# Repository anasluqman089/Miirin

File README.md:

# Miirin

Miirin is a compact MP3 player built around a Seeed XIAO ESP32-S3 and a
DFPlayer Pro. It has an OLED display, five buttons, a rotary encoder, and an
RGB status LED. The `CAD`, `PCB`, and `Production` folders contain the
enclosure, board, and manufacturing files.

## Bill of materials

| Quantity | Reference | Part | Prices ($) | Buy Links |
| :---: | :---: | :--- | :---: | :--- |
| 1 | U1 | Seeed XIAO ESP32-S3 module | 7.50 | [AliExpress](https://www.aliexpress.com/w/wholesale-Seeed-XIAO-ESP32-S3-module.html) |
| 1 | U2 | DFRobot DFPlayer Pro (DFR0768) | 8.50 | [AliExpress](https://www.aliexpress.com/w/wholesale-DFRobot-DFPlayer-Pro-DFR0768.html) |
| 1 | - | 1.3 Inch OLED screen | 3.50 | [AliExpress](https://www.aliexpress.com/w/wholesale-1.3-Inch-OLED-screen.html) |
| 1 | U3 | PCF8574P I2C I/O expander | 1.20 | [AliExpress](https://www.aliexpress.com/w/wholesale-PCF8574P-I2C-IO-expander.html) |
| 1 | D1 | Common-anode RGB LED | 0.35 | [AliExpress](https://www.aliexpress.com/w/wholesale-Common-anode-RGB-LED.html) |
| 1 | Q1 | P-channel MOSFET | 0.80 | [AliExpress](https://www.aliexpress.com/w/wholesale-P-channel-MOSFET.html) |
| 1 | SW6 | Rotary encoder | 0.60 | [AliExpress](https://www.aliexpress.com/w/wholesale-Rotary-encoder.html) |
| 1 | SW5 | Momentary push buttons | 0.15 | [AliExpress](https://www.aliexpress.com/w/wholesale-Momentary-push-buttons.html) |
| 4 | SW1-SW4 | Cherry MX Keyboard Switches | 2.00 | [AliExpress](https://www.aliexpress.com/w/wholesale-Cherry-MX-switch.html) |
| 1 | J1 | 4-pin socket/header for the OLED | 0.10 | [AliExpress](https://www.aliexpress.com/w/wholesale-4-pin-socket-header-for-the-OLED.html) |
| 1 | J2 | Switched 3.5 mm audio jack | 0.50 | [AliExpress](https://www.aliexpress.com/w/wholesale-Switched-3.5-mm-audio-jack.html) |
| 3 | R4-R6 | 220 Ohm resistors | 0.15 | [AliExpress](https://www.aliexpress.com/w/wholesale-220-Ohm-resistors.html) |
| 2 | R2-R3 | 4.7 kOhm resistors | 0.10 | [AliExpress](https://www.aliexpress.com/w/wholesale-4.7-kOhm-resistors.html) |
| 1 | R1 | 100 kOhm resistor | 0.05 | [AliExpress](https://www.aliexpress.com/w/wholesale-100-kOhm-resistor.html) |
| 2 | - | 100 kOhm resistors | 0.10 | [AliExpress](https://www.aliexpress.com/w/wholesale-100-kOhm-resistors.html) |
| 2 | C1-C2 | 10 uF ceramic capacitors | 0.30 | [AliExpress](https://www.aliexpress.com/w/wholesale-10-uF-ceramic-capacitors.html) |
| 1 | C4 | 0.1 uF ceramic capacitor | 0.10 | [AliExpress](https://www.aliexpress.com/w/wholesale-0.1-uF-ceramic-capacitor.html) |
| 1 | C5 | 470 uF polarized capacitor | 0.45 | [AliExpress](https://www.aliexpress.com/w/wholesale-470-uF-polarized-capacitor.html) |
| 3 | H1-H3 | M2 screw | 0.30 | [AliExpress](https://www.aliexpress.com/w/wholesale-M2-screw.html) |
| 5 | - | M2.5 screw | 0.50 | [AliExpress](https://www.aliexpress.com/w/wholesale-M2.5-screw.html) |
| 1 | - | PCB | 8.60 | - |
| 4 | - | 3D print | ~10.00 | - |
| **Total** | | | **$45.85** Not inluding shipping | |

## Controls and display

- **SW1:** Play or pause the current track.
- **SW2 / SW3:** Select the previous or next track. Selection wraps at either
  end of the list.
- **SW4:** Play the selected track.
- **Rotary encoder:** Adjust volume.
- **Hold SW5:** Pause playback and put the device into deep sleep. Press SW5 to
  wake it.

The OLED shows the current track, playback selection, volume, and battery
percentage. Battery percentage is an estimate based on cell voltage, not a
fuel-gauge measurement.

## Battery and RGB LED

Battery monitoring uses the divider wired to **D0**: battery positive goes through a 100 kΩ resistor to D0, then another 100 kΩ resistor connects D0 to battery negative (ground). The battery itself connects to the XIAO's battery pads.

The RGB LED is driven through the PCF8574 and indicates battery level:

- **Red:** Battery is at or below 20%
- **Green:** Battery is above 20%

Charging is not identified separately because the board has no charge-status
signal connected. The PCF8574 interrupt is connected to **D10**.

## Uploading code & audio files

Upload the code in firmware folder. Make sure to select the XIAO ESP32 S3 board.

Put your audio files on the DFPlayer Pro's storage. At startup, the player checks how many tracks are available and restores the last selected track and volume while the XIAO remains powered.

## CAD

Here is the link for the CAD
[Onshape](https://cad.onshape.com/documents/3d8e9b5928a29fef03f51911/w/7d3ee8411c85baeb3f6a489e/e/28521f022b7deb8d589466ae?renderMode=0&uiState=6ad3208a288b1a9cd259184f)

## Images

### Schematic

### PCB

### CAD

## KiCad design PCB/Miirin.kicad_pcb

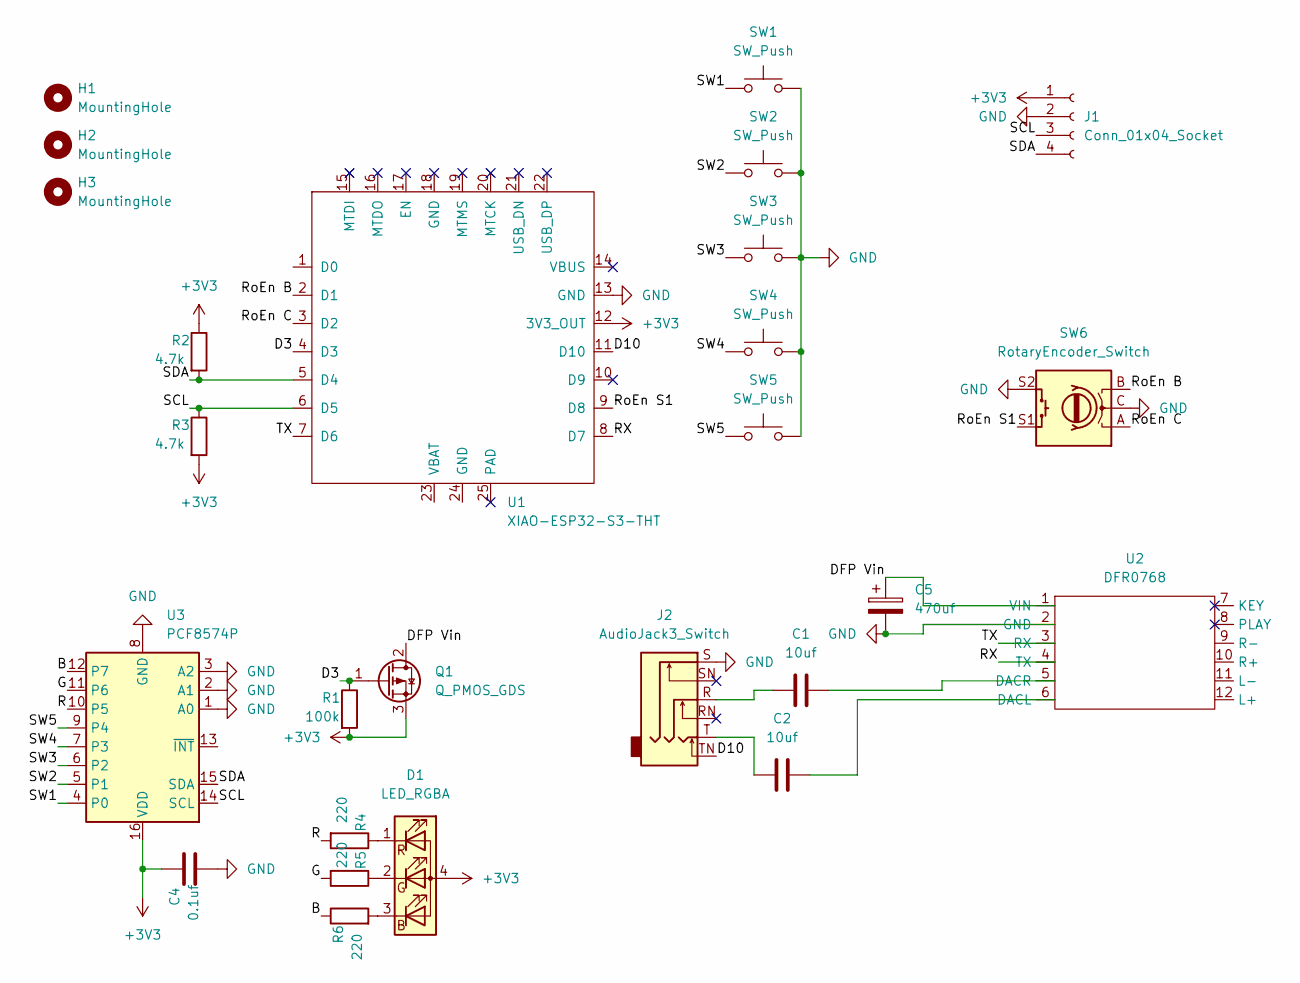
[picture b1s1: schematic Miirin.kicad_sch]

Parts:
C1, C2: 10uf; C_Disc_D4.3mm_W1.9mm_P5.00mm
C4: 0.1uf; C_Disc_D4.3mm_W1.9mm_P5.00mm
C5: 470uf; CP_Radial_D8.0mm_P3.50mm
D1: LED_RGBA; LED_D5.0mm-4_RGB
H1, H2, H3: MountingHole; MountingHole_2.2mm_M2
J1: Conn_01x04_Socket; PinHeader_1x04_P2.54mm_Horizontal
J2: AudioJack3_Switch; Jack_3.5mm_CUI_SJ1-3535NG_Horizontal
Q1: Q_PMOS_GDS; TO-92_Inline
R1: 100k; R_Axial_DIN0207_L6.3mm_D2.5mm_P10.16mm_Horizontal
R2, R3: 4.7k; R_Axial_DIN0207_L6.3mm_D2.5mm_P10.16mm_Horizontal
R4, R5, R6: 220; R_Axial_DIN0207_L6.3mm_D2.5mm_P10.16mm_Horizontal
SW1, SW2, SW3, SW4: SW_Push; SW_Cherry_MX_1.00u_PCB
SW5: SW_Push; SW_PUSH_6mm
SW6: RotaryEncoder_Switch; RotaryEncoder_Alps_EC11E-Switch_Vertical_H20mm
U1: XIAO-ESP32-S3-THT; XIAO-ESP32-S3-DIP
U2: DFR0768
U3: PCF8574P; DIP-16_W7.62mm

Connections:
+3V3: C4.2, D1.4 (A), J1.1, Q1.3 (S), R1.2, R2.1, R3.2, U1.12 (3V3_OUT), U3.16 (VDD)
/B: R6.1, U3.12 (P7)
/D3: Q1.1 (G), R1.1, U1.4 (D3)
/D10: J2.TN, U1.11 (D10)
/DFP Vin: C5.1, Q1.2 (D), U2.1 (VIN)
/G: R5.2, U3.11 (P6)
/R: R4.2, U3.10 (P5)
/RX: U1.8 (D7), U2.4 (TX)
/RoEn B: SW6.B, U1.2 (D1)
/RoEn C: SW6.A, U1.3 (D2)
/RoEn S1: SW6.S1, U1.9 (D8)
/SCL: J1.3, R3.1, U1.6 (D5), U3.14 (SCL)
/SDA: J1.4, R2.2, U1.5 (D4), U3.15 (SDA)
/SW1: SW1.1, U3.4 (P0)
/SW2: SW2.1, U3.5 (P1)
/SW3: SW3.1, U3.6 (P2)
/SW4: SW4.1, U3.7 (P3)
/SW5: SW5.1, U3.9 (P4)
/TX: U1.7 (D6), U2.3 (RX)
GND: C4.1, C5.2, J1.2, J2.S, SW1.2, SW2.2, SW3.2, SW4.2, SW5.2, SW6.C, SW6.S2, U1.13 (GND), U2.2 (GND), U3.1 (A0), U3.2 (A1), U3.3 (A2), U3.8 (GND)
unnamed: C1.1, J2.R
unnamed: C2.1, J2.T
unnamed: D1.3 (BK), R6.2
unnamed: D1.2 (GK), R5.1
unnamed: D1.1 (RK), R4.1
unnamed: C2.2, U2.6 (DACL)
unnamed: C1.2, U2.5 (DACR)

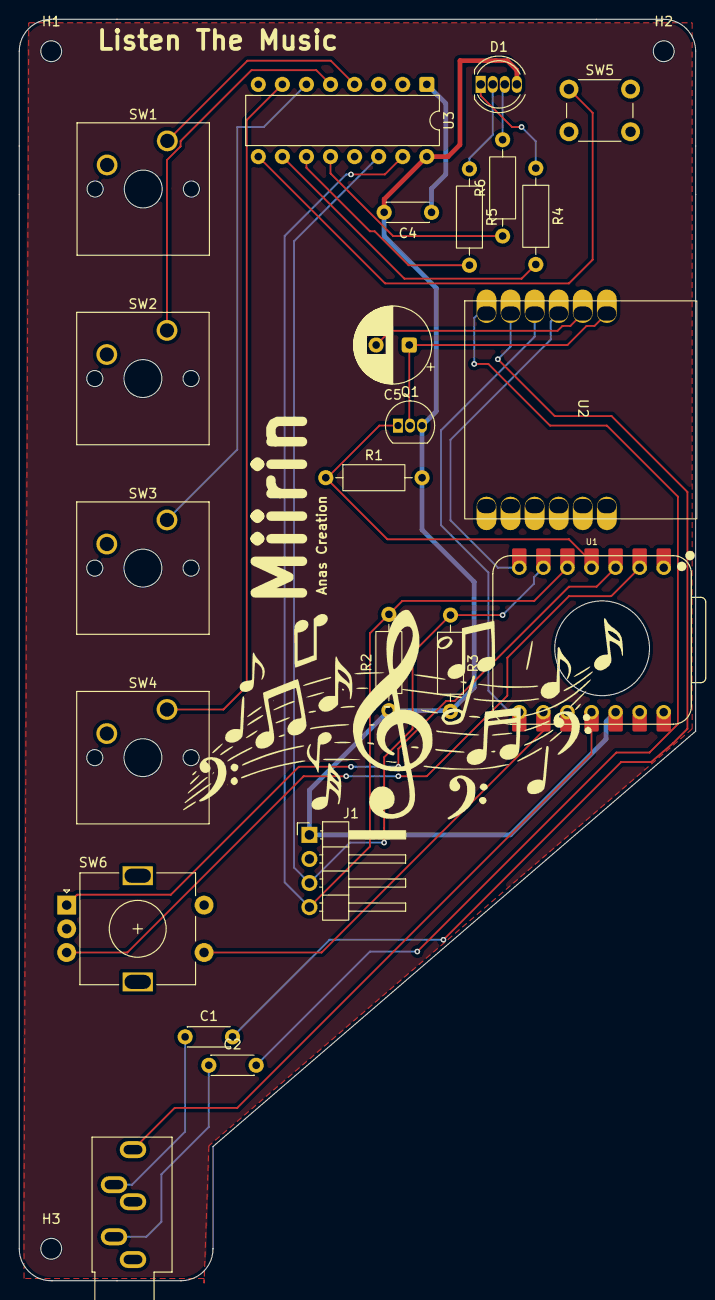
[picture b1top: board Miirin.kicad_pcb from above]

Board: 2 copper layers, 71.4 x 133.1 mm, 26 parts (0 on the bottom side), 27 nets.

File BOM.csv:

Quantity,Reference,Part,Prices ($),Buy Links
1,U1,Seeed XIAO ESP32-S3 module,7.50,https://www.aliexpress.com/w/wholesale-Seeed-XIAO-ESP32-S3-m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
1,U2,DFRobot DFPlayer Pro (DFR0768),8.50,https://www.aliexpress.com/w/wholesale-DFRobot-DFPlayer-Pro-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
1,-,1.3 Inch OLED screen,3.50,https://www.aliexpress.com/w/wholesale-1.3-Inch-OLED-screen.html
1,U3,PCF8574P I2C I/O expander,1.20,https://www.aliexpress.com/w/wholesale-PCF8574P-I2C-IO-expan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
1,D1,Common-anode RGB LED,0.35,https://www.aliexpress.com/w/wholesale-Common-anode-RGB-LED.html
1,Q1,P-channel MOSFET,0.80,https://www.aliexpress.com/w/wholesale-P-channel-MOSFET.html
1,SW6,Rotary encoder,0.60,https://www.aliexpress.com/w/wholesale-Rotary-encoder.html
1,SW5,Momentary push buttons,0.15,https://www.aliexpress.com/w/wholesale-Momentary-push-buttons.html
4,SW1-SW4,Cherry MX Keyboard Switches,2.00,https://www.aliexpress.com/w/wholesale-Cherry-MX-switch.html
1,J1,4-pin socket/header for the OLED,0.10,https://www.aliexpress.com/w/wholesale-4-pin-socket-header-f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
1,J2,Switched 3.5 mm audio jack,0.50,https://www.aliexpress.com/w/wholesale-Switched-3.5-mm-audio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
3,R4-R6,220 Ohm resistors,0.15,https://www.aliexpress.com/w/wholesale-220-Ohm-resistors.html
2,R2-R3,4.7 kOhm resistors,0.10,https://www.aliexpress.com/w/wholesale-4.7-kOhm-resistors.html
1,R1,100 kOhm resistor,0.05,https://www.aliexpress.com/w/wholesale-100-kOhm-resistor.html
2,-,100 kOhm resistors,0.10,https://www.aliexpress.com/w/wholesale-100-kOhm-resistors.html
2,C1-C2,10 uF ceramic capacitors,0.30,https://www.aliexpress.com/w/wholesale-10-uF-ceramic-capacit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
1,C4,0.1 uF ceramic capacitor,0.10,https://www.aliexpress.com/w/wholesale-0.1-uF-ceramic-capaci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
1,C5,470 uF polarized capacitor,0.45,https://www.aliexpress.com/w/wholesale-470-uF-polarized-capa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
3,H1-H3,M2 screw,0.30,https://www.aliexpress.com/w/wholesale-M2-screw.html
5,-,M3 screw,0.50,https://www.aliexpress.com/w/wholesale-M3-screw.html
1,-,PCB,8.60,-
4,-,3D print,~10.00,-
Total,-,-,45.85,-
